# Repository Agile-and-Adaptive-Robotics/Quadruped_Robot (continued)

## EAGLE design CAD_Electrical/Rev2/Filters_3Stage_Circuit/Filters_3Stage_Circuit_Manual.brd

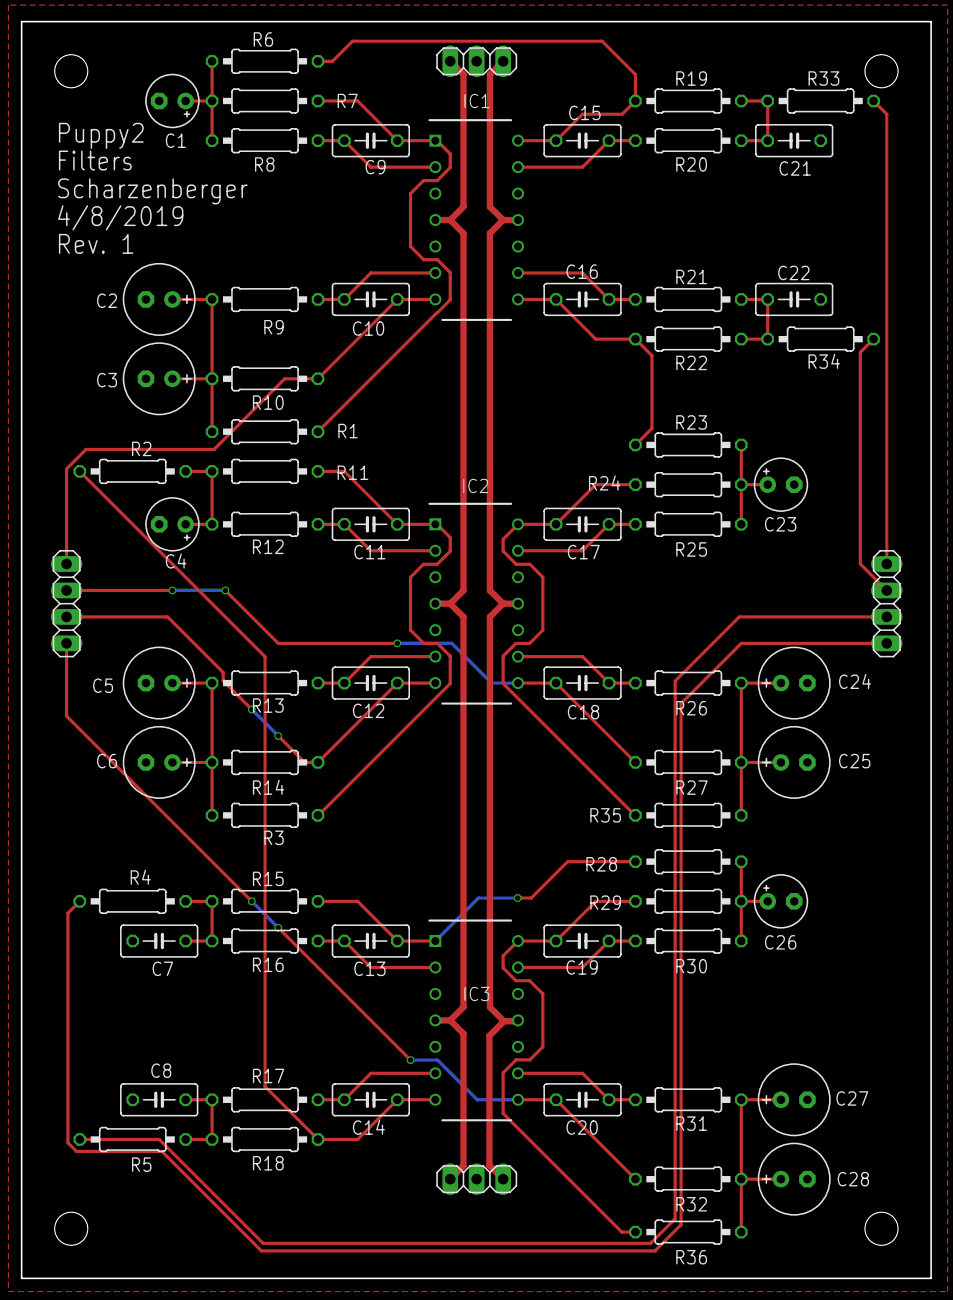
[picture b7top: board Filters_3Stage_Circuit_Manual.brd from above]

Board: 2 copper layers, 87.3 x 120.7 mm, 71 parts (0 on the bottom side), 43 nets.

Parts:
C1, C4, C23, C26: 2.2e-6; E2,5-5
C2, C3, C5, C6, C24, C25, C27, C28: 10e-6; E2,5-7
C7, C8, C21, C22: 0.22e-6; C050-030X075
C9, C10, C11, C12, C13, C14, C15, C16, C17, C18, C19, C20: 0.1e-6; C050-030X075
IC1, IC2, IC3: LM324N; DIP794W56P254L1905H533Q14N
JP1, JP4: 1X04
JP2, JP3: 1X03
R1, R3, R10, R14, R27, R32, R35, R36: 1.8e3; 0207/10
R2, R6, R7, R11, R23, R24, R28, R29: 6.8e3; 0207/10
R4, R5, R16, R17, R20, R21, R33, R34: 27e3; 0207/10
R8, R12, R25, R30: 2.7e3; 0207/10
R9, R13, R26, R31: 820; 0207/10
R15, R18, R19, R22: 15e3; 0207/10

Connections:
+24V: IC1.4, IC2.4, IC3.4, JP2.3, JP3.1
-24V: IC1.11, IC2.11, IC3.11, JP2.1, JP3.3
GND: C1.-, C2.-, C3.-, C4.-, C5.-, C6.-, C7.2, C8.2, C21.2, C22.2, C23.-, C24.-, C25.-, C26.-, C27.-, C28.-, IC1.3, IC1.5, IC1.10, IC1.12, IC2.3, IC2.5, IC2.10, IC2.12, IC3.3, IC3.5, IC3.10, IC3.12, JP2.2, JP3.2
IN0: JP4.4, R33.1
IN1: JP4.3, R34.1
IN2: JP4.2, R5.2
IN3: JP4.1, R4.2
unnamed: C15.1, IC1.14, R6.1, R19.2
unnamed: C15.2, IC1.13, R20.2
unnamed: C21.1, R19.1, R20.1, R33.2
unnamed: C9.1, IC1.1, R1.1, R7.1
unnamed: C9.2, IC1.2, R8.1
unnamed: C10.2, IC1.6, R9.1
unnamed: C1.+, R6.2, R7.2, R8.2
unnamed: C2.+, C3.+, R1.2, R9.2, R10.2
unnamed: C16.1, IC1.8, R22.2, R23.2
unnamed: C16.2, IC1.9, R21.2
unnamed: C22.1, R21.1, R22.1, R34.2
unnamed: C17.1, IC2.14, R24.2, R35.2
unnamed: C17.2, IC2.13, R25.2
unnamed: C23.+, R23.1, R24.1, R25.1
unnamed: C11.1, IC2.1, R3.1, R11.1
unnamed: C11.2, IC2.2, R12.1
unnamed: C4.+, R2.1, R11.2, R12.2
unnamed: C12.2, IC2.6, R13.1
unnamed: C5.+, C6.+, R3.2, R13.2, R14.2
unnamed: C18.2, IC2.9, R26.2
unnamed: C24.+, C25.+, R26.1, R27.1, R35.1
unnamed: C13.2, IC3.2, R16.1
unnamed: C14.1, IC3.7, R2.2, R18.1
unnamed: C14.2, IC3.6, R17.1
unnamed: C7.1, R4.1, R15.2, R16.2
unnamed: C8.1, R5.1, R17.2, R18.2
unnamed: C13.1, IC3.1, R15.1, R28.2
unnamed: C19.1, IC3.14, R29.2, R36.2
unnamed: C19.2, IC3.13, R30.2
unnamed: C26.+, R28.1, R29.1, R30.1
unnamed: C20.2, IC3.9, R31.2
unnamed: C27.+, C28.+, R31.1, R32.1, R36.1
O0: C10.1, IC1.7, JP1.1, R10.1
O1: C18.1, IC2.8, JP1.2, R27.2
O2: C12.1, IC2.7, JP1.3, R14.1
O3: C20.1, IC3.8, JP1.4, R32.2

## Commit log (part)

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2023-06-28 Update board mountV2.SLDPRT
    changed the clips of the board mount
2023-06-28 update to board mount
    changed the clips and refined the edges
2023-07-03 New Quadruped Hind Leg Hip Joint
    Adjusting dimensions to have a better fit between pelvis and femur.
    New hip spring calculations.
2023-07-05 Damped Hind Leg Assembly Changes
    Continued modifications to pelvis and femur to accommodate new springs and dampers
2023-07-10 Revised Hind Leg
    Revised Hind Leg
2023-07-11 Update Quadruped Damped Hind Leg
    Update Quadruped Damped Hind Leg
2023-07-17 assembly for inverted pendulum
    I finished the assembly for the inverted pendulum
2023-07-18 Damped Hind Leg Updates
    Damped Hing Leg Updates
2023-07-30 damper experimental data
    added data collected from test bench of dampers
2023-07-31 Damped hind leg calculation
    subassemblies to find center of mass
    start formatting data in excel to calculate experimental damping ratios
2023-07-31 Damper Calculations
    Tried to get damper calculations working. Will try to get more data so that data structures are the same as Emma's.
2023-07-31 Treadmill Update
    The treadmill has been updated to include posts
2023-08-01 Trying to optimize spring values
    Altering some scripts to calculate desired spring values for new damping constants
2023-08-11 damping value calculations
    ran data through damper value optimizers
2023-08-14 Adjustable Torsion Spring Brainstorming
    Adjustable Torsion Spring preliminary design
2023-08-16 calculated spring values for all dampers
    calculated spring values for all dampers
2023-08-17 test code
    test code
2023-08-22 New hip springs
    calculations and modelling for new hip springs - dimensional check
2023-08-25 Cont. Board Mount (large)
    Mount to leg for big control board
2023-09-11 Additional Spring Dimensions
    Added more springs
2023-09-12 New spring calculations
    spring constant calculations
2023-09-27 Updated readme.
2023-09-27 Updated files
    gcode files
2023-09-28 Organizing functional subnetwork examples.
2023-09-28 Restructuring FSA Toolbox utilities.
2023-09-29 trial data
    uploaded damped hind leg trial data
2023-09-29 more trial data
    added more quadruped leg drop data
2023-10-03 Matlab file to process data
    Matlab file to process data
2023-10-03 Data Processing
    Processed data for quadruped leg drop trials
2023-10-05 update code
    update code for reading serial data
2023-10-12 update app
    update app
2023-10-12 updated app
    updated app
2023-10-13 trial data
    upload trial data
2023-10-13 update data and plot
    update data and plot
2023-10-19 bevel gear
    bevel gear
2023-10-19 Adding numerical simulation tools.
2023-10-19 bevel gear slot
    bevel gear slot for printing
2023-10-20 print files
    print files
2023-10-20 parts
    new parts
2023-10-23 new handle
    new handle for weight testing
2023-10-27 Updating code for SfN poster creation.
2023-11-01 no damper trials
    no damper trials
2023-11-01 figures
    figures
2023-11-02 Updating FSA examples.
2023-11-14 torsion spring data
    torsion spring data
2023-11-30 changed some things
    I'm not sure what these are
2023-12-06 assembly parts
    assembly parts for emmas paper
2023-12-08 more trials
    more trial data for Emma paper
2024-01-11 new spring and weight handle
    new spring and weight handle for newly filed d shaft
2024-01-17 Updated plots
    updated plots
2024-01-21 organizing folders
    organizing folders
2024-01-25 Torsion spring configurations
    torsion spring configurations
2024-01-26 New spring assembly
    new spring assembly
2024-01-26 spring test parts
    spring test parts
2024-01-29 Updated spring design
    updated spring design
2024-01-30 Created division conversion derivation matlab script.
2024-01-31 Updated inversion conversion derivation.
2024-02-02 Started absolute division wo c2.
2024-02-02 more springs
    updated
2024-02-02 spring housing
    new parts
2024-02-06 table update
    updated names
2024-02-08 lots of updated parts
    new spring parts
2024-02-09 spring calculations
    spring calculations
2024-02-10 Updated inversion conversion example.
2024-02-10 torque control
    torque control
2024-02-12 matlab app
    headache
2024-02-13 Updating reduced inversion subnetwork conversion.
2024-02-14 Created reduced division subnetwork examples.
2024-02-15 spring calcs
    spring calcs
2024-02-16 Started reduced absolute inversion error code.
2024-02-16 Spring testing assembly
    Stuff
2024-02-20 Updated network utilities documentation.
2024-02-22 data collection
    editing code for torsion spring data collection
2024-02-23 new parts
    encoder mount for testing
2024-02-24 Updating directory organization.
2024-02-24 trial data
    trial data
2024-02-27 Significant directory reorganization.
2024-02-27 pulley components
    pulley components
2024-02-28 parts
    large pulley parts
2024-02-28 added data sets
    added data sets to merge
2024-03-01 updated stuff
    i don't even know
2024-03-01 2nd order approximations
    it doesn't work
2024-03-02 Completed reduced division after inversion examples.
2024-03-04 help
    :(
2024-03-05 Absolute multiplication subnetwork example.
2024-03-06 more testing
    data testing
2024-03-06 Reduced multiplication conversion example complete.
2024-03-07 pendulum simulation
    code
2024-03-08 figures for presentation
    presentation
2024-03-11 response picture
    spring and damper
2024-03-13 Started transmission subnetwork examples.
2024-03-13 Added gitkeep files to save and load directories.
2024-03-13 Significant update to network utilities documentation.
2024-03-14 Generalized linear combination examples.
2024-03-14 trial data
    spring data
2024-03-14 Linear combination error examples in progress.
2024-03-15 update data
    update data
2024-03-18 new parts
    new parts and data
2024-03-18 more data processing
    data
2024-03-19 Finished absolute linear combination error computation.
2024-03-19 Completed linear combination subnetwork error comparison.
2024-03-21 Started transmission paper plots.
2024-03-23 Updating utility functions.
2024-04-02 Updating network documentation.
2024-04-02 Fixing network method inputs.
2024-04-05 Updating neuron class method inputs.
2024-04-09 Significant updates to neuron manager method inputs and outputs.
2024-04-11 Updating neuron manager method inputs.
2024-04-11 Completed updating neuron manager subnetwork creation functions.
2024-04-12 stuff
    stuff
2024-04-12 Updated neuron activation domain methods.
2024-04-14 Complete update pass on neuron manager.
2024-04-16 Started updating synapse methods.
2024-04-17 Started updating synapse manager methods.
2024-04-18 Updated synaptic reversal potential methods.
2024-04-18 Updating synapse manager synaptic conductance methods.
2024-04-18 Significant progress on synapse manager synapse creation methods.
2024-04-22 Updating neuron manager documentation.
2024-04-25 Updated synapse manager synapse creation methods.
2024-04-26 Updated applied current class methods.
2024-05-02 Updated applied voltage and applied current managers.
2024-05-08 Updating network class to reflect lower level changes.
2024-05-13 Continuing network class updates.
2024-05-14 Updating subnetwork creation methods.
2024-05-15 Finished updating subnetwork component creation methods.
2024-05-17 Starting new absolute transmission example.
2024-05-23 Updating neuron design equations.
2024-05-24 Updating low level synapse design methods.
2024-05-28 Updating synapse utility methods.
2024-05-29 Updating synapse design utilities.
2024-05-31 Synapse utility method updates in progress.
2024-05-31 Updating neuron manager design methods.
2024-06-04 Synapse design method updates in progress.
2024-06-06 Updating synapse parameter packing and unpacking methods.
2024-06-11 Finished draft of synapse and applied current design methods.
2024-06-17 calculations
    updated files
2024-06-20 organizing files
    organizing files
2024-06-21 new step files
    new step files
2024-06-28 2023 solidworks
    2023 solidworks files and assembly
2024-07-01 resized spring in SOLIDWORKS 2021
2024-07-01 Added Holes for Tendons
2024-07-01 Added two testers for Hex Shaft
2024-07-02 Create Onyx_Spring_Ankle.SLDPRT
    Scaled spring down to have a diameter of 33mm
2024-07-02 Added cutout for hex shaft, printed off tester
2024-07-02 Added Set Screw hole in PL_BL_007
2024-07-03 Removed Back Left from my folder
2024-07-03 adjusted screw holes and hole for 1/8" shaft
2024-07-09 spring stuff
    metal spring analysis and knee spring
2024-07-09 scaled
2024-07-10 Widened m2 hole
2024-07-10 Update AARL_QR_FR_LE_PL_BL_012.SLDPRT
    Centered holes for the tendons.
2024-07-10 Adjusted shaft hole to D from hex
2024-07-11 Adjusted diameter of spring to 55mm
2024-07-11 adjusted adapter hole
2024-07-17 Quadruped hip adjustments
    Finished adjusting the hip component (file in my GitHub folder) and took screenshots to document the process in google slides.
2024-07-19 Created new slot based spring concept, adjusted damper adapter for spring
2024-07-22 updated ankle spring adapter
2024-07-22 Creating assembly for google slides update.
2024-07-22 solidworks tutorial
2024-07-26 updated decimals for paper
    updated decimals for paper
2024-07-30 Printed shaft testers and revised shaft hole in spring
2024-07-31 Made Bushings for bearing and made redesigned pulley for testing
2024-08-02 Ran buckling tests
2024-08-06 opened assm
2024-08-06 ran matlab trials
2024-08-07 Upper Knee Design
    Redesigned upper knee part to fit new large spring.
2024-08-09 Completed knee
    CAD-ed both upper and lower knee, then putting them in an assembly with collision detection.
2024-08-09 Created stl for ankle piece
2024-08-13 Completed Knee
    Completed and printed both upper and lower knee parts, creating an assembly and animation from them.
2024-08-19 File organization
    Deleted irrelevant half parts, renaming files and creating a README.txt.
2024-10-01 Subnetwork design updates.
2024-10-03 Propagating low-level updates to network methods.
2024-10-04 Adding printing functions.
2024-10-08 Updating parameter processing methods.
2024-10-15 Adding parameter packing and unpacking methods.
2024-10-17 Updating subnetwork design methods.
2024-10-18 trial data
    old stashed trial data
2024-10-18 Creating network parameter methods.
2024-10-24 Implementing network packing methods.
2025-04-16 Starting to implement transmission updates.
2025-04-16 Relative transmission example updated.
2025-04-17 Transmission error comparison update in progress.
2025-04-18 Transmission Error Comparison at Specific Gain In Progress
2025-04-23 Absolute Inversion Example Updated.
2025-04-24 Absolute Inversion Error Example Updated.
2025-04-24 Inversion Error Comparison Example Updated.
2025-04-25 Continued inversion error comparison variable gain example.
2025-04-29 Updated inversion error comparison to accommodate variable gains.
2025-04-30 Creating inversion variable gain plots.
2025-05-02 Created surface steady state response plotting methods.
2025-05-05 Updating inversion variable gain plots.
2025-05-07 Updating inversion variable gain parameter plots.
2025-05-08 Updated variable gain inversion plot legends and titles.
2025-05-09 Reduced absolute inversion subnetwork example complete.
2025-05-14 Reduced inversion variable gain plots in progress.
2025-05-20 Modified function subnetwork example directory structure.
2025-05-20 Inversion & reduced inversion derivation files complete.
2025-05-22 Absolute and relative division after inversion derivation complete.
2025-05-22 Absolute division example started.
2025-05-29 Update network and network utilities to accommodate new division subnetwork updates.
2025-06-01 Minor updates.
2025-06-04 Absolute Division Error Updates In Progress
2025-06-05 Relative division example complete.
2025-06-06 Division Error Comparison In Progress.
